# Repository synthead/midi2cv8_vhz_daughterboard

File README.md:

This is a KiCad project for a clone of PAiA's discontinued midi2cv8 V/Hz daughterboard.  It was designed from the same schematic as the original and is being shared with you under the kind permission of PAiA.  When installed, the board looks like this:

At the moment, there are [three bugs](https://github.com/synthead/midi2cv8_vhz_daughterboard/issues) in the circuit design.  I am only going to build one of these things, so it's unlikely that I'll fix them, so I figured that I would leave a note about it here.  These three bugs are solved by adding the wires below and bridging pin 8 of the 4051 to ground with a blob of solder.  The workarounds, when in-place, look like this:

In addition, if you're adding this V/Hz daughterboard to a midi2cv8 that is already configured for V/octave CV, you'll have to change resistor *R28 (a 5.6k ohm resistor should be there), and add a new resistor to #R32 on the midi2cv8 motherboard.  This wasn't obvious to me and spent a couple days trying to figure it out, so I thought I'd mention it here as well.  Here are the values from page 12 of the midi2cv8 manual:

|Designation|Value|Color Code A-B-C|
|---|---|---|
|\*R28|2700|red-violet-red|
|#R32|2700|red-violet-red|

Also, if this is the first time you're etching a board, I highly recommend tearing out a glossy page from a magazine and printing onto it for your toner transfer.  Also, don't bother with clothing irons.  I use an unmodified Swingline 1000L laminator.  Tape up the magazine paper so it doesn't slip around, then run it through the laminator a dozen times or so.  If you do it right, you'll end up with a transfer looking like this:

To get a head start, rendered PDFs for the PCB and the silk screen can be found in [the `rendered/` directory](https://github.com/synthead/midi2cv8_vhz_daughterboard/tree/master/rendered).  If you fancy it, you can transfer toner from the silkscreen PDF to the front of a single-layer PCB for a poor man's silkscreen.  It actually works really good and looks really nice!

Enjoy!

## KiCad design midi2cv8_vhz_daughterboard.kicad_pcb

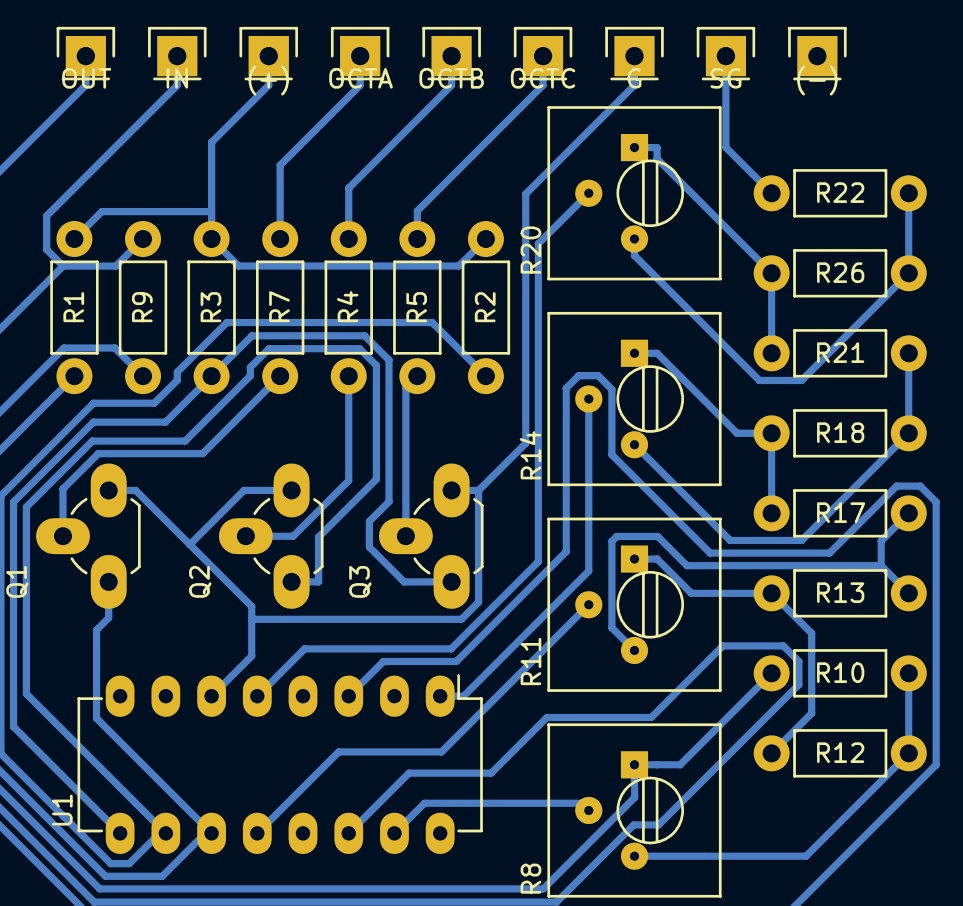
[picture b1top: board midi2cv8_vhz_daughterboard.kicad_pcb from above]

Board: 2 copper layers, 32 parts (0 on the bottom side), 26 nets.

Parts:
(+): (+); Pin_Header_Straight_1x01
(-): (-); Pin_Header_Straight_1x01
G: G; Pin_Header_Straight_1x01
IN: IN; Pin_Header_Straight_1x01
OCTA: OCTA; Pin_Header_Straight_1x01
OCTB: OCTB; Pin_Header_Straight_1x01
OCTC: OCTC; Pin_Header_Straight_1x01
OUT: OUT; Pin_Header_Straight_1x01
Q1, Q2, Q3: NPN; TO-92_Rugged
R1, R2, R3, R4, R5, R7: 10k; Resistor_Horizontal_RM7mm
R8, R11, R14, R20: 1K; Potentiometer_Trimmer-Suntan-TSR-3386P
R9: 390; Resistor_Horizontal_RM7mm
R10: 270; Resistor_Horizontal_RM7mm
R12: 100; Resistor_Horizontal_RM7mm
R13: 120; Resistor_Horizontal_RM7mm
R17, R22: 47; Resistor_Horizontal_RM7mm
R18: 56; Resistor_Horizontal_RM7mm
R21, R26: 22; Resistor_Horizontal_RM7mm
SG: SG; Pin_Header_Straight_1x01
U1: 4051; DIP-16_W7.62mm_LongPads

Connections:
GNDREF: G.1, Q1.3, Q2.3, Q3.3, U1.6
unnamed: OUT.1, U1.3
unnamed: IN.1, R9.2, U1.14
unnamed: (+).1, R1.1, R2.1, R3.1
unnamed: OCTA.1, R7.2
unnamed: OCTB.1, R4.2
unnamed: OCTC.1, R5.2
unnamed: R22.1, SG.1
unnamed: Q1.1, R1.2, U1.11
unnamed: Q1.2, R7.1
unnamed: Q2.1, R2.2, U1.10
unnamed: Q2.2, R4.1
unnamed: Q3.1, R3.2, U1.9
unnamed: Q3.2, R5.1
unnamed: R8.2, U1.15
unnamed: R8.3, R10.1, R12.2
unnamed: R8.1, R9.1, R10.2
unnamed: R11.1, R12.1, R13.2
unnamed: R11.2, U1.12
unnamed: R11.3, R13.1, R17.2
unnamed: R14.1, R17.1, R18.2
unnamed: R14.2, U1.1
unnamed: R14.3, R18.1, R21.2
unnamed: R20.1, R21.1, R26.2
unnamed: R20.2, U1.5
unnamed: R20.3, R22.2, R26.1

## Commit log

2016-10-29 Initial commit.
2016-11-01 Add README.md.
2016-11-01 Fix resistor table in README.md.
2016-11-01 Remove * from #R32 resistor code.
2016-11-01 Add a little more detail about the resistors to replace.
